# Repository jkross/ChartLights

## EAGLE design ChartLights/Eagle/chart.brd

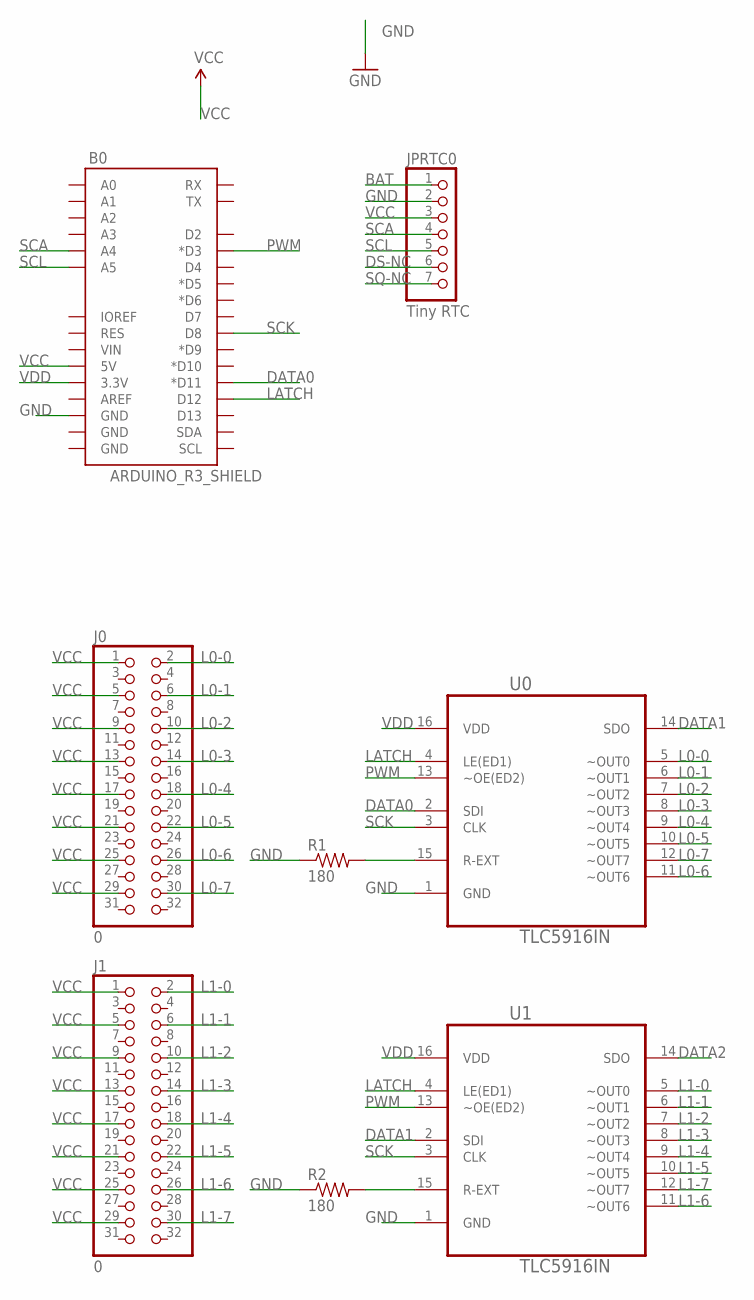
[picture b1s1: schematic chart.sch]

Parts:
B0: ARDUINO_R3_SHIELD; UNO_R3_SHIELD
J0, J1: 0; 2X16
JPRTC0: Tiny RTC; 1X07
R1, R2: 180; AXIAL-0.4
U0, U1: TLC5916IN; DIP254P762X508-16

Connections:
BAT: JPRTC0.1
DATA0: B0.D11 (*D11), U0.2 (SDI)
DATA1: U0.14 (SDO), U1.2 (SDI)
DATA2: U1.14 (SDO)
DS-NC: JPRTC0.6
GND: B0.GND@2 (GND), JPRTC0.2, R1.P$1 (1), R2.P$1 (1), U0.1 (GND), U1.1 (GND)
L0-0: J0.2, U0.5 (~OUT0)
L0-1: J0.6, U0.6 (~OUT1)
L0-2: J0.10, U0.7 (~OUT2)
L0-3: J0.14, U0.8 (~OUT3)
L0-4: J0.18, U0.9 (~OUT4)
L0-5: J0.22, U0.10 (~OUT5)
L0-6: J0.26, U0.11 (~OUT6)
L0-7: J0.30, U0.12 (~OUT7)
L1-0: J1.2, U1.5 (~OUT0)
L1-1: J1.6, U1.6 (~OUT1)
L1-2: J1.10, U1.7 (~OUT2)
L1-3: J1.14, U1.8 (~OUT3)
L1-4: J1.18, U1.9 (~OUT4)
L1-5: J1.22, U1.10 (~OUT5)
L1-6: J1.26, U1.11 (~OUT6)
L1-7: J1.30, U1.12 (~OUT7)
LATCH: B0.D12, U0.4 (LE(ED1)), U1.4 (LE(ED1))
unnamed: R2.P$2 (2), U1.15 (R-EXT)
unnamed: R1.P$2 (2), U0.15 (R-EXT)
PWM: B0.D3 (*D3), U0.13 (~OE(ED2)), U1.13 (~OE(ED2))
SCA: B0.A4, JPRTC0.4
SCK: B0.D8, U0.3 (CLK), U1.3 (CLK)
SCL: B0.A5, JPRTC0.5
SQ-NC: JPRTC0.7
VCC: B0.5V, J0.1, J0.5, J0.9, J0.13, J0.17, J0.21, J0.25, J0.29, J1.1, J1.5, J1.9, J1.13, J1.17, J1.21, J1.25, J1.29, JPRTC0.3
VDD: B0.3.3V, U0.16 (VDD), U1.16 (VDD)

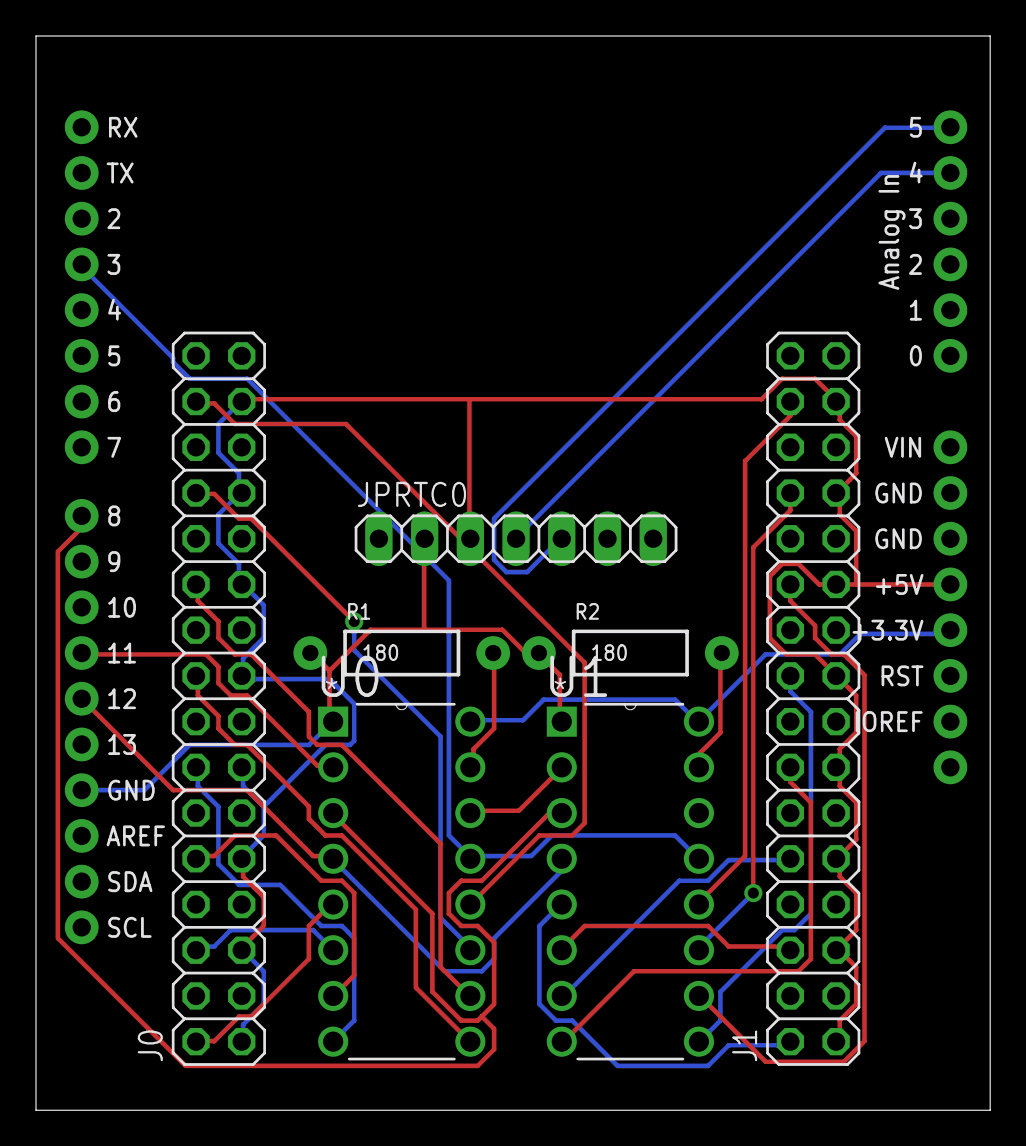
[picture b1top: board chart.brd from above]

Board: 2 copper layers, 53.0 x 59.7 mm, 8 parts (0 on the bottom side), 28 nets.

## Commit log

2016-08-28 initial version
2016-08-29 statistics framework
2016-08-29 refactored into separate file
2016-08-29 paramaterize NUM_BANKS, comments for measured perf stats
2016-08-29 VS project creation
2016-08-30 Add Eagle PCB for project
2016-08-30 another Eagle file
2016-09-02 alternate PWM values
2016-09-07 2x20 headers x2, all on one UnoR3 header
2016-09-07 update Eagle epf
2016-09-07 UI mods + Arduino\libraries
2016-09-08 light list
2016-09-08 sorted by minDist; added place references by hand
2016-09-10 added silkscreen
2016-09-10 Sparkfun DRC
2016-09-10 gerbers
2016-09-11 silkscreen, gerbers, sketch-up
2016-09-11 remove temporary eagle files
2016-09-11 gitignore files
2016-09-21 LED holder, light list update, netlist update
2016-09-21 SketchUp .gitignore
2016-09-23 mod jack and LED holder; light list sorted by angle
2016-09-23 update light lists and text summary
2016-09-26 updated LED holder, updated light list, test pattern fin SimpleSerial
2016-09-26 increased LED holder cable size and retaining base
2016-09-26 test pattern
2016-09-26 add lat/lon to custom points
2016-09-26 Mat measurements
2016-09-27 stl timers, add lfsr code
2016-09-27 morse
2016-09-27 ledData
2016-09-27 cleanup
2016-09-27 power comments
2016-09-27 update light list for new #34. add light sequence
2016-09-27 refactor to multiple files
2016-09-27 VC project updates
2016-09-27 rtc refactoring
2016-09-27 add libraries
2016-09-27 cleanup libs
2016-09-27 further refactor of scheduler, ledDriver
2016-09-28 ledPattern
2016-09-28 got one led working, not 2
2016-09-28 change pattern.h types; debug print macros
2016-09-29 38 lights working, with lfsr
2016-09-29 40 lights working - removed RTC to get memory
2016-09-29 spread start over 2s; cleanup a bit
2016-10-01 get ready for Morse...; cleanup a bit
2016-10-01 beginning of morse classes
2016-10-02 snapshot perf: modify set not get
2016-10-02 backout rolling timer:operation
2016-10-06 MorseTest & cleanup (test runs WIN32) works with wrapping time removed print statements, serial init, RTClib reference
2016-10-06 Version 1 - as shipped MorseTest & cleanup (test runs WIN32) works with wrapping time
2016-10-12 Comment code
2016-10-12 Work on bright lights of the Pacific Coast
2016-10-12 Text Readme
2016-10-13 new script to parse RNC chart files to get bounding boxes, and new resulting chartLatLon.xml file format
2016-10-13 csv files for a number of charts & top-forty
2016-10-14 Add - The Making of - document
2016-10-15 New PCB for ribbon-connected LEDs
2016-10-15 remove snapshotTime
2016-10-15 fix nonsense with extra expired-timers deque
2016-10-15 cleanup some code - remove BUGBUG conditions around LFSR etc.
2016-10-15 refactor random start and delays into LFSR module, removing redundancey
2016-10-15 ReadMe update
2016-10-15 New directory structure
2016-10-15 VS project changes after move
2016-10-16 Start new boards

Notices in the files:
parts and their libraries:
SparkFun-Boards: Licensing: Creative Commons ShareAlike 4.0 International - https://creativecommons.org/licenses/by-sa/4.0
